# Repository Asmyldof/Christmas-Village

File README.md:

Christmas-Village
=================
A two cheap microcontroller project to control which of ten channels is on or off based on a true-random generator (with guaranteed no bias), while also controlling the general brightness either manually or from a light sensor.
The remainder of this ReadMe will be written as a chronological logbook, to show the speed at which the development was done.

How a missing connector inspired me to make a present in stead of buying one:
=================

Early December 2013:
-----
I glue some LED strips into the crockery Christmas Village houses my parents bought and supplied father with some pre-fab connectors and cables. That year the houses were lit at a fraction of the cost of high-watage incandescent bulbs from the supplier. (Where the LEDstrip uses less than 1/10th the power).

Early January 2014:
-----
The houses get packed into wraps and boxes.

December 19th 2014:
-----
Father WhatsApps to ask about the connector set-up, because the old one seems to have fallen out of the package at some point. We call and agree that I will get a new connector to go from one single power supply to ten houses the next week, for the main holidays (as they were busy upto Dec 22nd)

December 20th 2014:
-----
I start designing a PCB to control the houses with the shortest-path-available method, still considering reusability, and thus splitting the dimmer and the 10 channel on/off controller into two separate, relatively cheap Atmel AVRs.
The plan:
* First and foremost: Use only items from my direct stock (My stock is large, very large even, but not limitless), so it can be built the same weekend.
* Get an ATTiny10 to do the dimming and keeping an eye on the light/dark situation
* Get an ATTiny4313 to control the channels on/off, including a true-random generator without bias (more on this later)
* Add a FM noise source for very-high-speed random generation (for future plans) (see below why that's not in there anymore)

December 21st 2014 (late night):
-----
With the hardware fully designed it's time to start the etching

December 22nd 2014 (afternoon):
-----
With the hardware fully built it's time to test the noise generation from the FM antenna. The FM antenna proves to be unreliable and insensitive in the small box that has been chosen, so a lower-frequency noise source is taken: The good old Zener Diode.

December 22nd 2014 (early evening):
-----
The ATTiny10 software is ready for testing, but a paid projct takes temporary precedence.

December 22nd 2014 (late evening):
-----
The ATTiny10 is working and installed, time to go bring what is done as a present to the parental home and continue programming there later.

December 22nd/23rd 2014 (midnight and later):
-----
Development of the random control is well underway (all chips were already mounted before ATTiny10 testing started).

December 23rd 2014 (approx 5:30 AM):
-----
Random control of the houses works, time to decouple the programmer and go to bed, allowing the random behaviour as a surprise for the folks that'll wake up soon.

December 23rd (5:30 AM) through december 26th:
-----
Break (the houses are automatically dimmed by the sensor and the light sensor sucessfully influences the number of houses on - more on during the day time than during the night time - and the random behaviour works, that was the target for christmas.
(However, some work had already been done for other functionality, including patterns and EEPROM re-configurable settings, which should later be read/write-able through the serial interface (quick after thought in the hardware design).

December 27th 2014:
-----
Continuation of the development: Adding Serial interface, interleaved with shopping, cleaning and such.
(Note, however, that the hardware is not available at this point, so all code is written and tested on paper only, undoubtedly leaving bugs to be discovered when the hardware is back again for a while.)

December 28th 2014 (2:30 AM):
-----
Serial command set almost completely implemented, before the remaining command get implemented the default eeprom_ routines from AVR-GCC need to be switched over to interrupt driven and flag-bocked, or some routine splitting needs to be done to get the blocking eeprom read/writes in the non-interrupt space inside main(). Else the "ReadPattern" and "WritePattern" commands will hold up too many interrupts.

December 28th 2014 (14:00 to 16:30):
-----
A small window of hardware testing, allowing debugging of the USART code and changing some variables into GPIOR, to decrease code size. Basic USART system working, not all commands fully tested yet.

December 30th, 31st 2014 and January 1st, 2nd and 3rd 2015:
-----
More debugging to be done, before the hardware leaves, small sessions in between other activities, it's a busy week after all. Plan is to complete the USART (excepting GoToBootloader)and EEPROM interfaces and hopefully make the pattern system work completely. Once that is all completed andthere is still room enough for a two or three page fixed bootloader, at least in the 4313 setup, that will be added later (weekends during January 2015, or a little later)

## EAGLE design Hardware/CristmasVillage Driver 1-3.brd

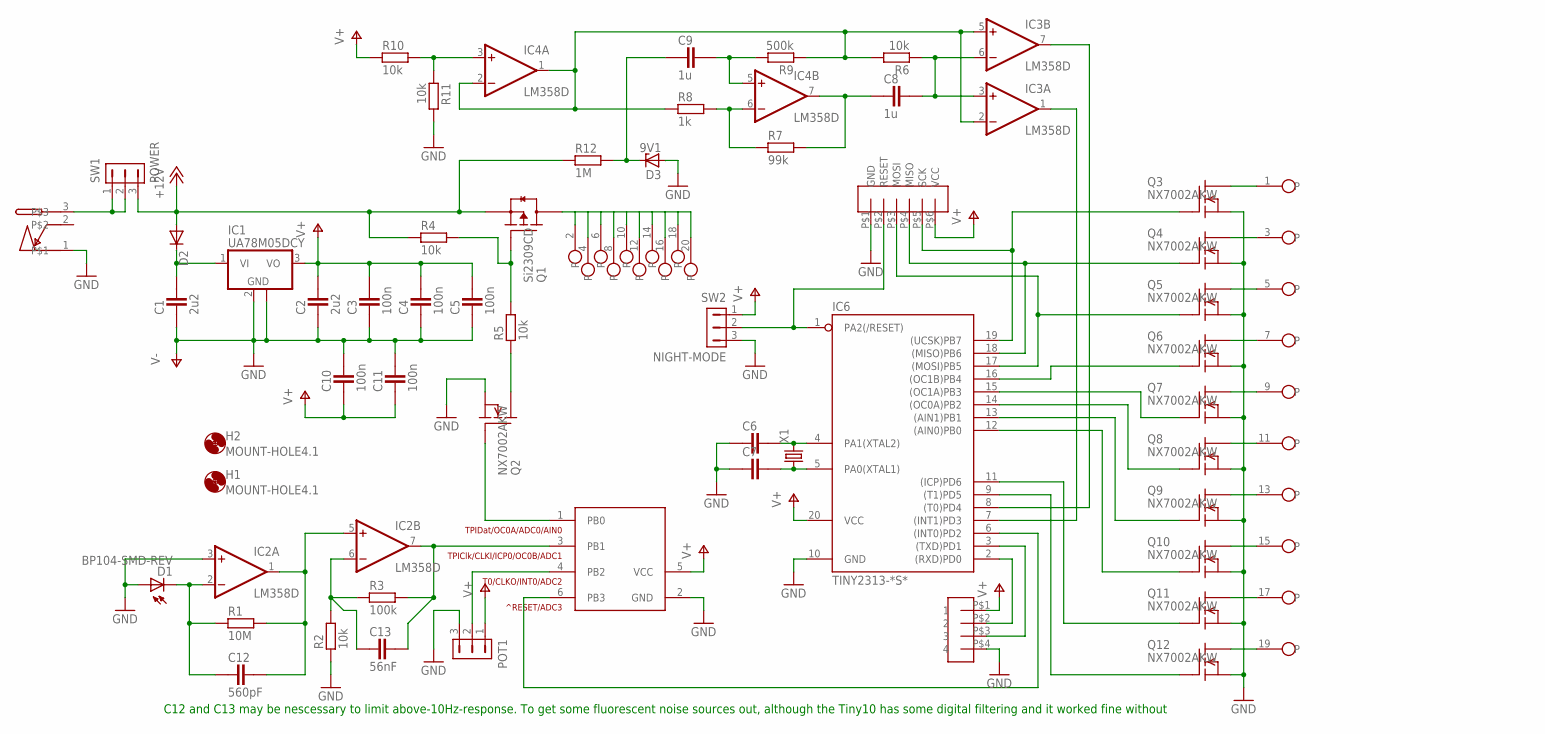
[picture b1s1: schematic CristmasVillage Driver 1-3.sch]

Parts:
C1, C2: 2u2; CAPC3215X168N
C3, C4, C5, C10, C11: 100n; CAPC1608X92N
C6, C7: CAPACITOR_0603; CAPC1608X92N
C8, C9: 1u; CAPC3215X168N
C12: 560pF; CAPC1608X92N
C13: 56nF; CAPC1608X92N
CN1: MJ-180SMT
CN2-PROG: JST-6PSPI-SIDE-S6B; 6P-H
CN3-SERIAL: JST-4PSIDE-S4B; 4P-H
CN5-LEDSTRIPS: HDR_2X10_SIDE-MOUNT; 20PIN-10TOP-10BOT
D1: BP104-SMD-REV; BR104SMDREV
D2: DIODE-MINIMELF; MINIMELF
D3: 9V1; SOT23
H1, H2: MOUNT-HOLE4.1; 4,1
IC1: UA78M05DCY; SOT223
IC2, IC3, IC4: LM358D; SO08
IC5: ATTINY-4/5/9/10; SOT23-6
IC6: TINY2313-*S*; SO20L$
POT1: HDR-1X3-MTE-100; MTE-100-3V
Q1: Si2309CD; SOT95P280X135-3N
Q2, Q3, Q4, Q5, Q6, Q7, Q8, Q9, Q10, Q11, Q12: NX7002AKW; SOT323R
R1: 10M; RESC1608X55N
R2, R4, R5, R6, R10, R11: 10k; RESC1608X55N
R3: 100k; RESC1608X55N
R7: 99k; RESC1608X55N
R8: 1k; RESC1608X55N
R9: 500k; RESC1608X55N
R12: 1M; RESC1608X55N
SW1: POWER; MTE-100-3V
SW2: NIGHT-MODE; MTE-100-3V
X1: CRYSTALSM49; SM49

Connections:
+12V: D2.A, Q1.2 (S), R4.1, R12.1, SW1.3
GND: C1.1, C2.1, C3.1, C4.1, C5.1, C6.1, C7.1, C10.2, C11.2, CN1.1, CN2-PROG.P$1 (GND), CN3-SERIAL.P$4 (4), D1.1 (A), D3.1 (A), IC1.2 (GND), IC1.4 (GND), IC2.3 (+IN), IC2.4 (V-), IC3.4 (V-), IC4.4 (V-), IC5.2 (GND), IC6.10 (GND), POT1.3, Q2.2 (S), Q3.2 (S), Q4.2 (S), Q5.2 (S), Q6.2 (S), Q7.2 (S), Q8.2 (S), Q9.2 (S), Q10.2 (S), Q11.2 (S), Q12.2 (S), R2.1, R11.2, SW2.3
HALF-VCC: IC3.2 (-IN), IC3.5 (+IN), IC4.1 (OUT), IC4.2 (-IN), R6.2, R8.1, R9.1
MISO: CN2-PROG.P$4 (MISO), IC6.18 ((MISO)PB6), Q4.1 (G)
MOSI: CN2-PROG.P$3 (MOSI), IC6.17 ((MOSI)PB5), Q5.1 (G)
unnamed: C1.2, D2.C, IC1.1 (VI)
unnamed: C12.1, D1.2 (C), IC2.2 (-IN), R1.1
unnamed: C12.2, IC2.1 (OUT), IC2.5 (+IN), R1.2
unnamed: C13.1, IC2.6 (-IN), R2.2, R3.1
unnamed: C13.2, IC2.7 (OUT), IC5.3 (PB1), R3.2
unnamed: IC6.9 ((T1)PD5), Q12.1 (G)
unnamed: IC5.1 (PB0), Q2.1 (G)
unnamed: IC6.11 ((ICP)PD6), Q11.1 (G)
unnamed: C6.2, IC6.4 (PA1(XTAL2)), X1.2
unnamed: C7.2, IC6.5 (PA0(XTAL1)), X1.1
unnamed: IC6.12 ((AIN0)PB0), Q10.1 (G)
unnamed: IC6.13 ((AIN1)PB1), Q9.1 (G)
unnamed: IC6.14 ((OC0A)PB2), Q8.1 (G)
unnamed: IC6.15 ((OC1A)PB3), Q7.1 (G)
unnamed: CN2-PROG.P$2 (RESET), IC6.1 (PA2(/RESET)), SW2.2
unnamed: IC5.6 (PB3), IC6.6 ((INT0)PD2)
unnamed: IC5.4 (PB2), POT1.2
unnamed: IC6.16 ((OC1B)PB4), Q6.1 (G)
unnamed: CN5-LEDSTRIPS.1, Q3.3 (D)
unnamed: CN1.3, SW1.1, SW1.2
unnamed: CN5-LEDSTRIPS.3, Q4.3 (D)
unnamed: CN5-LEDSTRIPS.5, Q5.3 (D)
unnamed: CN5-LEDSTRIPS.7, Q6.3 (D)
unnamed: CN5-LEDSTRIPS.9, Q7.3 (D)
unnamed: CN5-LEDSTRIPS.11, Q8.3 (D)
unnamed: CN5-LEDSTRIPS.13, Q9.3 (D)
unnamed: CN5-LEDSTRIPS.15, Q10.3 (D)
unnamed: CN5-LEDSTRIPS.17, Q11.3 (D)
unnamed: CN5-LEDSTRIPS.19, Q12.3 (D)
unnamed: CN5-LEDSTRIPS.2, CN5-LEDSTRIPS.4, CN5-LEDSTRIPS.6, CN5-LEDSTRIPS.8, CN5-LEDSTRIPS.10, CN5-LEDSTRIPS.12, CN5-LEDSTRIPS.14, CN5-LEDSTRIPS.16, CN5-LEDSTRIPS.18, CN5-LEDSTRIPS.20, Q1.3 (D)
unnamed: Q1.1 (G), R4.2, R5.2
unnamed: Q2.3 (D), R5.1
unnamed: IC3.1 (OUT), IC6.7 ((INT1)PD3)
unnamed: IC3.7 (OUT), IC6.8 ((T0)PD4)
unnamed: C8.2, IC3.3 (+IN), IC3.6 (-IN), R6.1
unnamed: IC4.3 (+IN), R10.2, R11.1
unnamed: C8.1, IC4.7 (OUT), R7.2
unnamed: IC4.6 (-IN), R7.1, R8.2
unnamed: C9.2, IC4.5 (+IN), R9.2
unnamed: C9.1, D3.3 (C), R12.2
RX: CN3-SERIAL.P$2 (2), IC6.2 ((RXD)PD0)
SCK: CN2-PROG.P$5 (SCK), IC6.19 ((UCSK)PB7), Q3.1 (G)
TX: CN3-SERIAL.P$3 (3), IC6.3 ((TXD)PD1)
V+: C2.2, C3.2, C4.2, C5.2, C10.1, C11.1, CN2-PROG.P$6 (VCC), CN3-SERIAL.P$1 (1), IC1.3 (VO), IC2.8 (V+), IC3.8 (V+), IC4.8 (V+), IC5.5 (VCC), IC6.20 (VCC), POT1.1, R10.1, SW2.1

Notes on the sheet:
C12 and C13 may be nescessary to limit above-10Hz-response. To get some fluorescent noise sources out, although the Tiny10 has some digital filtering and it worked fine without

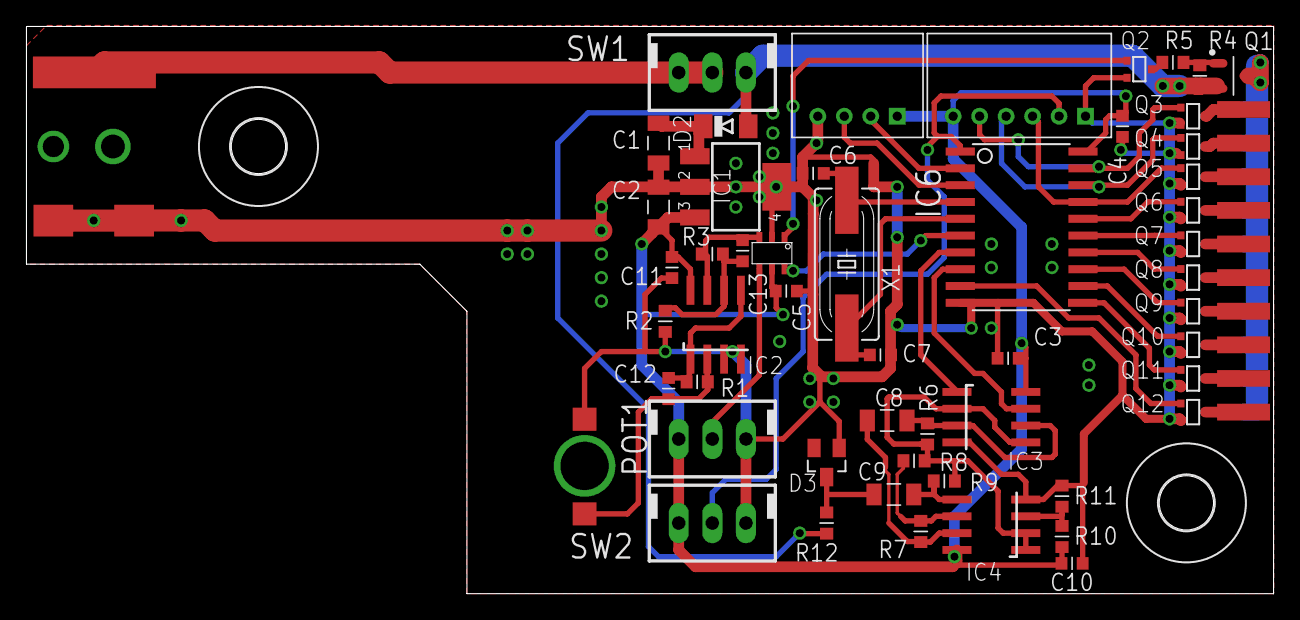
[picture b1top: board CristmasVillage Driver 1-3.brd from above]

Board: 2 copper layers, 94.2 x 42.9 mm, 56 parts (0 on the bottom side), 49 nets.

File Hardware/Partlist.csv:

Partlist; ; Christmas Village Project
Part; Value; Package; Library; Position (mil); Orientation

C1; 2u2; CAP-1206; ipc-7351-capacitor; (1880 1340); R90
C2; 2u2; CAP-1206; ipc-7351-capacitor; (1880 1150); R270
C3; 100n; CAP-0603; ipc-7351-capacitor; (2920 700); R0
C4; 100n; CAP-0603; ipc-7351-capacitor; (3260 1390); R90
C5; 100n; CAP-0603; ipc-7351-capacitor; (2260 900); R180
C6; ; CAP-0603; ipc-7351-capacitor; (2340 1250); R0
C7; ; CAP-0603; ipc-7351-capacitor; (2540 710); R180
C8; 1u; CAP-1206; ipc-7351-capacitor; (2560 515); R0
C9; 1u; CAP-1206; ipc-7351-capacitor; (2580 295); R0
C10; 100n; CAP-0603; ipc-7351-capacitor; (3110 90); R0
C11; 100n; CAP-0603; ipc-7351-capacitor; (1920 970); R270
C12; 560pF; CAP-0603; ipc-7351-capacitor; (1910 610); R90
C13; 56nF; CAP-0603; ipc-7351-capacitor; (2130 1020); R90
CN1; MJ-180SMT; MJ-180SMT; con-Multicomp; (80 1330); R0
CN2-PROG; JST-6PSPI-SIDE-S6B; 6P-H; avr-6; (3150 1420); R180
CN3-SERIAL; JST-4PSIDE-S4B; 4P-H; Connector-2mm; (2590 1420); R180
CN5-LEDSTRIPS; HDR_2X10_SIDE-MOUNT; 20PIN-10TOP-10BOT; con-SideHeader; (3620 1440); R270
D1; BP104-SMD-REV; BR104SMDREV; Vishay; (1660 380); R270
D2; ; MINIMELF; diode; (2080 1390); R0
D3; 9V1; SOT23; diode; (2380 390); R180
IC1; UA78M05DCY; SOT223; linear; (2110 1210); R270
IC2; LM358D; SO08; linear4; (2050 800); R0
IC3; LM358D; SO08; linear4; (2870 525); R270
IC4; LM358D; SO08; linear4; (2870 205); R90
IC5; ATTINY-4/5/9/10; SOT23-6; avr-6; (2180 1060); R270
IC6; TINY2313/4313; SO20; avr-6; (2960 1090); R270
POT1; ; HDR-1x3; con-hdrs40; (2040 460); R0
Q1; Si2309CD; SOT95P280X135-3N; ipc-7351-transistor; (3590 1540); R0
Q2; NX7002AKW; SOT323R; ZeroCross Project; (3310 1560); R270
Q3; NX7002AKW; SOT323R; ZeroCross Project; (3470 1420); R270
Q4; NX7002AKW; SOT323R; ZeroCross Project; (3470 1330); R270
Q5; NX7002AKW; SOT323R; ZeroCross Project; (3470 1240); R270
Q6; NX7002AKW; SOT323R; ZeroCross Project; (3470 1140); R270
Q7; NX7002AKW; SOT323R; ZeroCross Project; (3470 1040); R270
Q8; NX7002AKW; SOT323R; ZeroCross Project; (3470 940); R270
Q9; NX7002AKW; SOT323R; ZeroCross Project; (3470 840); R270
Q10; NX7002AKW; SOT323R; ZeroCross Project; (3470 740); R270
Q11; NX7002AKW; SOT323R; ZeroCross Project; (3470 640); R270
Q12; NX7002AKW; SOT323R; ZeroCross Project; (3470 540); R270
R1; 10M; RES-0603; ipc-7351-resistor; (1995 630); R180
R2; 10k; RES-0603; ipc-7351-resistor; (1900 810); R90
R3; 100k; RES-0603; ipc-7351-resistor; (2040 1010); R180
R4; 10k; RES-0603; ipc-7351-resistor; (3490 1540); R90
R5; 10k; RES-0603; ipc-7351-resistor; (3410 1580); R0
R6; 10k; RES-0603; ipc-7351-resistor; (2680 475); R270
R7; 99k; RES-0603; ipc-7351-resistor; (2660 185); R270
R8; 1k; RES-0603; ipc-7351-resistor; (2640 395); R180
R9; 500k; RES-0603; ipc-7351-resistor; (2730 335); R180
R10; 10k; RES-0603; ipc-7351-resistor; (3080 170); R90
R11; 10k; RES-0603; ipc-7351-resistor; (3080 290); R90
R12; 1M; RES-0603; ipc-7351-resistor; (2380 210); R90
SW1; POWER; HDR-1x3; con-hdrs40; (2040 1550); R0
SW2; NIGHT-MODE; HDR-1x3; con-hdrs40; (2040 210); R0
X1; 7.3728MHz; SM49; crystal; (2440 980); R90

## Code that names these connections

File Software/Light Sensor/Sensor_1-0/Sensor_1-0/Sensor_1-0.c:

/*
 * Sensor_1_0.c
 *
 * Created: 22-12-2014 13:36:16
 *  Author: Robert
 */ 

#include <avr/io.h>
#include <avr/interrupt.h>


/* internal functions: */
inline static uint8_t	AddValueToStack(uint8_t Value);
inline static void StartADC();

/*
 * In the hardware in this project the values are as follows:
 * Completely dark room: 87mV   (4.4bit)
 * Absolute minimum value: 81mV   (4.1bit)
 * Gloomy room: 140mV   (7.1 bit)
 * Low lighting: 400mV    (20.4 bit)
 * Well lit room: 780mV    (39.8 bit)
 * Brightly lit room: 950mV    (48.4 bit)
 * Sunny room: 1905mV    (97.2 bit)
 */

#define		SENSOR_ADCVAL_DARK				7  // At which value will it start triggering night mode
#define		SENSOR_ADCVAL_MAXIMUM			68  // At which value will it go to maximum brightness
#define		SENSOR_ADCVAL_MINIMUM			5  // At which value will it go to minimum brightness

#define		PWM_OUT_AUTO_MINIMUM			128 //AUTO Mode minimum output PWM value
#define		PWM_OUT_AUTO_MAXIMUM			255 //AUTO Mode maximum output PWM value

// the system:
//  temp = [sensor value] - [minimum sensor value]
//  if(temp < 0) temp = 0;
//  temp = temp << [shift up by]
//  temp = temp + [pwm out minimum]
//  if( temp > [pwm out maximum] ) temp = [pwm out maximum];
//  <pwm output> = temp
#define		PWM_SENSOR_SHIFTUP_BY			1	

#define		POTENTIOMETER_DISABLE_ALL_AUTO	250		// above this level the sensor does nothing
#define		POTENTIOMETER_MANUALDIM_MAX		192		// above this level the lights are full on
#define		POTENTIOMETER_MANUALDIM_MIN		64		// 
#define		POTENTIOMETER_AUTO_SEPERATION	5		// the split value in the AUTO range

#define		PWM_OUT_SHIFTUP_BY				1


#define		ADC_SENSOR_STACKSIZE			15

#define		ADC_PRESCALER					3 // Default 1MHz gives 125kHz ADC clock.
/*
ADC Clock should be between 50kHz and 200kHz for best operation
 0 - CkIO / 2
 1 - CkIO / 2
 2 - CkIO / 4
 3 - CkIO / 8
 4 - CkIO / 16
 5 - CkIO / 32
 6 - CkIO / 64
 7 - CkIO / 128
 ** Any higher numbers will be masked down to the above series (i.e. 8 = 0, 9 = 1, etc) **
*/

#define		WATCHDOG_PRESACLE			1
/*
The ADC is started by the watchdog time-out, higher frequency gives better potentiometer response
but lower levels of filtering out noise on the sensor:
0 - 16ms
1 - 32ms
2 - 64ms
3 - 0.125s
4 - 0.25s
5 - 0.5s
6 - 1s
7 - 2s
32 - 4s
33 - 8s

Value is masked, so mistakes are protected from causing unpredictable behaviour, beyond
a strange, unexpected time-out
*/




/*
 * In the hardware setup of this project:
 * LED PWM Output = PB0 / OCR0A
 * NIGHTMODE Pin = PB3 / Reset
 * Sensor = PB1 / ADC1
 * Poti = PB2 / ADC2
 */
#define		OCR0_OUTPUTREGISTER				OCR0AL
#define		TCCR0A_VALUE					0b10000001
#define		TCCR0B_VALUE					0b00001001 // Set to prescaler 1, fast PWM 8bit


#define		PORTB_OUT_PWMPIN				(1 << PORTB0)
#define		PORTB_OUT_NIGHTMODE				(1 << PORTB3)
#define		PINB_IN_POTENTIOMETER			(1 << PINB2)
#define		PINB_IN_SENSOR					(1 << PINB1)
#define		ADC_DIDR_POTENTIOMETER			(1 << ADC2D)
#define		ADC_DIDR_SENSOR					(1 << ADC1D)
#define		ADC_ADMUX_SENSOR				0x01
#define		ADC_ADMUX_POTENTIOMETER			0x02



uint8_t		SensorStack[ADC_SENSOR_STACKSIZE];
uint8_t		PotentiometerVal;


/* automated define, no touhy! */
#if (WATCHDOG_PRESACLE > 33)
#warning 'Watchdog prescaler set to a bad value (too high), setting to 8seconds'
	#undef WATCHDOG_PRESACLE
	#define WATCHDOG_PRESACLE 33
#endif


int main(void)
{
    // during development nightmode output is disabled, to avoid triggering reset:
	// TODO: uncomment when reset disable will be set:
	DDRB = (PORTB_OUT_PWMPIN | PORTB_OUT_NIGHTMODE);
	PORTB = 0x00;
	
	// Disable the input logic on the ADC channels:
	DIDR0 = (ADC_DIDR_POTENTIOMETER | ADC_DIDR_SENSOR);
	
	ADMUX = ADC_ADMUX_POTENTIOMETER;
	// ADCSRA is set in StartConversion()
	
	// enable Watchdog interrupt and mask the prescaler:
	WDTCSR = (1<<WDIE)|(WATCHDOG_PRESACLE & 0x27);
	
	OCR0AH = 0;
	OCR0AL = 0;
	OCR0BH = 0;
	OCR0BL = 0;
	
	TCCR0A = TCCR0A_VALUE;
	TCCR0B = TCCR0B_VALUE;
	
	//enable all interrupts:
	sei();
	
	while(1)
    {
        //TODO:: Please write your application code 
    }
}


ISR(WDT_vect)
{
	WDTCSR |= (1<<WDIE);
	StartADC();
}


ISR(ADC_vect)
{
	uint8_t		temp;
	uint8_t		avg;

	temp = ADCL;
	
	if( ADMUX == ADC_ADMUX_SENSOR )
	{
		if( temp < SENSOR_ADCVAL_MINIMUM )
			temp = SENSOR_ADCVAL_MINIMUM;
		
		avg = AddValueToStack(temp);
		temp = avg;
		
		if( temp > SENSOR_ADCVAL_MAXIMUM )
			temp = SENSOR_ADCVAL_MAXIMUM;
		
		temp -= SENSOR_ADCVAL_MINIMUM;

		temp = temp << PWM_SENSOR_SHIFTUP_BY;
		
		temp += PWM_OUT_AUTO_MINIMUM;

		if( temp > PWM_OUT_AUTO_MAXIMUM )
			temp = PWM_OUT_AUTO_MAXIMUM;
		
		if( PotentiometerVal < POTENTIOMETER_MANUALDIM_MIN )
		{
			OCR0_OUTPUTREGISTER = temp;
		
			if( PotentiometerVal > POTENTIOMETER_AUTO_SEPERATION )
			{
				if( avg < SENSOR_ADCVAL_DARK )
				{
					PORTB |= PORTB_OUT_NIGHTMODE;
				}
				else
				{
					PORTB &= ~PORTB_OUT_NIGHTMODE;
				}
			}
			else
			{
				PORTB &= ~PORTB_OUT_NIGHTMODE;
			}
		}
		else if( PotentiometerVal < POTENTIOMETER_DISABLE_ALL_AUTO )
		{
			if( avg < SENSOR_ADCVAL_DARK )
			{
				PORTB |= PORTB_OUT_NIGHTMODE;
			}
			else
			{
				PORTB &= ~PORTB_OUT_NIGHTMODE;
			}
		}
		else
		{
			PORTB &= ~PORTB_OUT_NIGHTMODE;
		}
	
		ADMUX = ADC_ADMUX_POTENTIOMETER;
	}
	else
	{
		PotentiometerVal = temp;
		
		if( PotentiometerVal < POTENTIOMETER_MANUALDIM_MAX )
		{
			if( PotentiometerVal >= POTENTIOMETER_MANUALDIM_MIN )
			{ /* we are manually dimming */
				temp = PotentiometerVal - POTENTIOMETER_MANUALDIM_MIN;
				temp = temp << PWM_OUT_SHIFTUP_BY;
				OCR0_OUTPUTREGISTER = temp;
			}
		}
		else
		{
			OCR0_OUTPUTREGISTER = 255;
		}
		
		ADMUX = ADC_ADMUX_SENSOR;
	}
}


/*
 *  Puts a value onto the sensor stack, calculates the stack average and returns it.
 */
inline static uint8_t	AddValueToStack(uint8_t Value) 
{
	uint16_t	temp = Value;
	
	for( uint8_t itt = 0; itt < ADC_SENSOR_STACKSIZE; itt++ )
	{
		temp += SensorStack[itt];
		if( itt == (ADC_SENSOR_STACKSIZE - 1) )
			SensorStack[itt] = Value;
		else
			SensorStack[itt] = SensorStack[itt + 1];			
	}
	
	return (uint8_t) (temp / (ADC_SENSOR_STACKSIZE+1));
}

/*
 * Starts the ADC for a one time run
 */
inline static void StartADC()
{
	ADCSRA = ((1<<ADEN)|(1<<ADSC)|(1<<ADIE)|(ADC_PRESCALER & 0x07));
}

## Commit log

2014-12-21 First part of the Schematic drawn
2014-12-21 Decided on adding light sensor
2014-12-21 Decided on power connector, hooked up dimming, added Tiny2313/4313
2014-12-21 schematic complete, transferred to board
2014-12-22 Almost entire LED controller routed, including random antenna experiment
2014-12-22 Decided on a plastic box from old stock and adjusted board size + some more routing
2014-12-22 Hardware design all done, exported for manual etching.
2014-12-22 Changed from FM tuned antenna idea to Zener Noise for random: v1.1
2014-12-22 First attempt at light sensor code
2014-12-22 Sensor Chip software function complete (needs splitting into header files) - first creation of driver project
2014-12-22 Comments with pin configuration and temporary Set-All-LEDs-On code for DEMO
2014-12-22 Added some default value defines and eeprom definitions
2014-12-22 Filling in the Watchdog Interrupt
2014-12-23 Done creating the first version to try, only random mode implemented (pattern mode to be done)
2014-12-23 Removed a small mistake in getting EE-data to RAM
2014-12-23 In debugging: Got random working the simple way
2014-12-23 Got Random number generator working: small mistake
2014-12-23 Debugging Random toggling of houses. Counting houses on works
2014-12-23 All except EEPROM working
2014-12-23 Fully functioning software for random operation. (pattern opperation & RS232 still to do)
2014-12-23 Moving to processing house changes in main-loop through flags set in the WDT timeout
2014-12-23 Added a dedicated startup delay, to "show all lights" a while for testing wiring
2014-12-23 Tried moving processing into main loop using flags, but could not seem to find why compiler optimized it to broken. (No optimisation: worked, optimisation, any level: nothing)
2014-12-23 Removed some deacivated debugging code for cleanliness
2014-12-27 Ramp up to Serial Comm: Command Set definitions
2014-12-27 Start of building USART interface, designed command set, started implementing interrupts
2014-12-27 Added majority of usart commands, todo: bulk read and write of pattern data. USART now officially too large for 2313 types (TODO: Make USART optional)
2014-12-28 Compilable implementation of all USART functions except patterndata transfers. UNTESTED! (Hardware is "out in the field" right now)
2014-12-28 Merged in Github LICENSE, current version still untested (hardware temporarily unavailable)
2014-12-28 Created a readme file showing the process
    Project started December 20th, Dec 23rd hardware and software according to minimum requirements were complete. See readme for more facts.
2014-12-28 Fixed some mistakes and oversights in readme
    Added a bit more clarity to the process and fixed a couple of typos before it's finally bed time.
2014-12-28 Added note about no-hardware to readme
2014-12-28 Added nice title line to the story/log part
2014-12-28 Added opt. filter caps to hardware & created PDF exports of v1.2
2014-12-28 Removed some USART bugs, 80% tested.
2014-12-28 Cleaned up silkscreen - added gerber exports
2014-12-28 Added a partslist
2014-12-29 Made some USART TX changes, stuff got broken somewhere
2014-12-29 After some debugging all previous commands work properly again, but with better code.
2014-12-31 Turned the USART into a half-duplex device. This avoids overwriting commands when the host PC doesn't wait for ACK/NACK messages. Larger/more expensive devices can use more complex buffering to allow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
2014-12-31 Updated README with progress and expected future progress

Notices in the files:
parts and their libraries:
con-hdrs40: Copyright (C) 2004, Bob Starr (bobstarr@mindspring.com)
